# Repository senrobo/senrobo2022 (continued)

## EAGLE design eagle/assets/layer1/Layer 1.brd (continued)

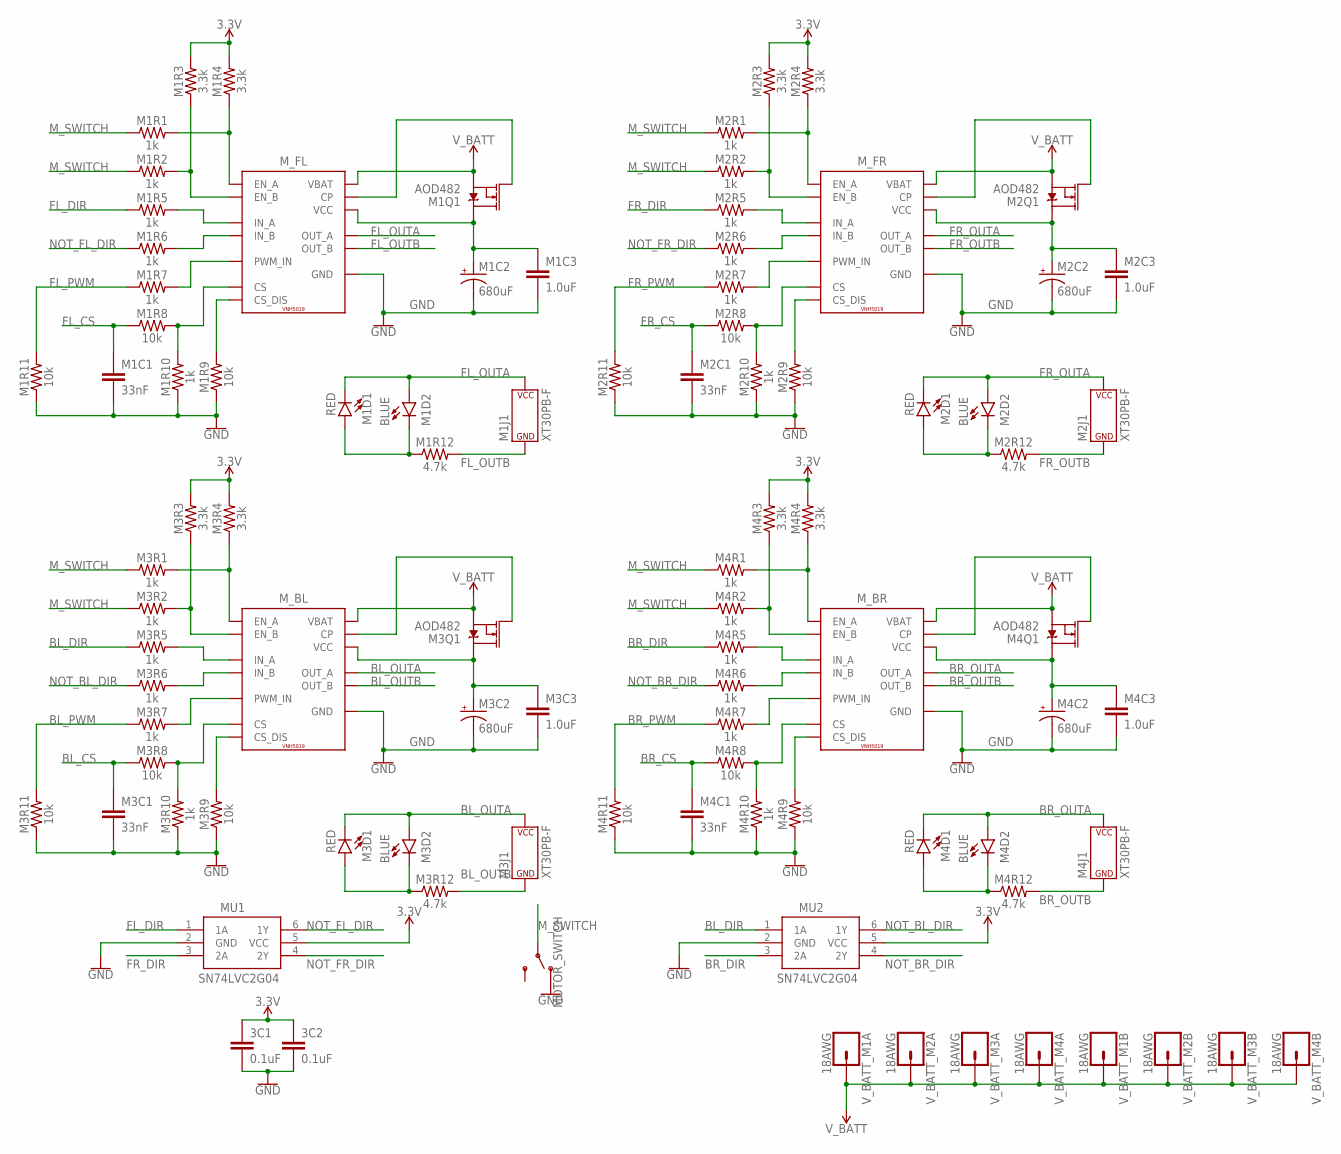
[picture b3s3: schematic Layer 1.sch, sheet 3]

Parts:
3C1, 3C2: 0.1uF; C0603
M1C1, M2C1, M3C1, M4C1: 33nF; C0603
M1C2, M2C2, M3C2, M4C2: 680uF; 3.5MM_CAP
M1C3, M2C3, M3C3, M4C3: 1.0uF; C0603
M1D1, M2D1, M3D1, M4D1: RED; LED-0603
M1D2, M2D2, M3D2, M4D2: BLUE; LED-0603
M1J1, M2J1, M3J1, M4J1: XT30PB-F
M1Q1, M2Q1, M3Q1, M4Q1: AOD482; DPAK
M1R1, M1R2, M1R5, M1R6, M1R7, M1R10, M2R1, M2R2, M2R5, M2R6, M2R7, M2R10, M3R1, M3R2, M3R5, M3R6, M3R7, M3R10, M4R1, M4R2, M4R5, M4R6, M4R7, M4R10: 1k; R0603
M1R3, M1R4, M2R3, M2R4, M3R3, M3R4, M4R3, M4R4: 3.3k; R0603
M1R8, M1R9, M1R11, M2R8, M2R9, M2R11, M3R8, M3R9, M3R11, M4R8, M4R9, M4R11: 10k; R0603
M1R12, M2R12, M3R12, M4R12: 4.7k; R0603
MOTOR_SWITCH: SWITCH-SPDT-PTH-11.6X4.0MM-LOCK; SWITCH_SPDT_PTH_11.6X4.0MM_LOCK
MU1, MU2: SN74LVC2G04DBVR; SOT23-6
M_BL: VNH5019; POWERSO-30
M_BR: VNH5019; POWERSO-30
M_FL: VNH5019; POWERSO-30
M_FR: VNH5019; POWERSO-30
V_BATT_M1A, V_BATT_M1B, V_BATT_M2A, V_BATT_M2B, V_BATT_M3A, V_BATT_M3B, V_BATT_M4A, V_BATT_M4B: 18AWG

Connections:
3.3V: 3C1.1, 3C2.1, M1R3.2, M1R4.2, M2R3.2, M2R4.2, M3R3.2, M3R4.2, M4R3.2, M4R4.2, MU1.5 (VCC), MU2.5 (VCC); also elsewhere on the board
BL_CS: M3C1.1, M3R8.1; also elsewhere on the board
BL_DIR: M3R5.1, MU2.1 (1A); also elsewhere on the board
BL_OUTA: M3D1.C, M3D2.A, M3J1.+ (V+), M_BL.P1 (OUT_A), M_BL.P25 (OUT_A), M_BL.P30 (OUT_A), M_BL.P$1 (OUT_A), M_BL.P$2 (OUT_A), M_BL.P$3 (OUT_A), M_BL.P$4 (OUT_A), M_BL.P$5 (OUT_A), M_BL.P$6 (OUT_A), M_BL.P$7 (OUT_A), M_BL.P$8 (OUT_A), M_BL.P$9 (OUT_A), M_BL.SLUG2 (OUT_A)
BL_OUTB: M3J1.- (V-), M3R12.2, M_BL.P15 (OUT_B), M_BL.P16 (OUT_B), M_BL.P21 (OUT_B), M_BL.P$10 (OUT_B), M_BL.P$11 (OUT_B), M_BL.P$12 (OUT_B), M_BL.P$13 (OUT_B), M_BL.P$14 (OUT_B), M_BL.P$15 (OUT_B), M_BL.P$16 (OUT_B), M_BL.P$17 (OUT_B), M_BL.P$18 (OUT_B), M_BL.SLUG3 (OUT_B)
BL_PWM: M3R7.1, M3R11.2; also elsewhere on the board
BR_CS: M4C1.1, M4R8.1; also elsewhere on the board
BR_DIR: M4R5.1, MU2.3 (2A); also elsewhere on the board
BR_OUTA: M4D1.C, M4D2.A, M4J1.+ (V+), M_BR.P1 (OUT_A), M_BR.P25 (OUT_A), M_BR.P30 (OUT_A), M_BR.P$1 (OUT_A), M_BR.P$2 (OUT_A), M_BR.P$3 (OUT_A), M_BR.P$4 (OUT_A), M_BR.P$5 (OUT_A), M_BR.P$6 (OUT_A), M_BR.P$7 (OUT_A), M_BR.P$8 (OUT_A), M_BR.P$9 (OUT_A), M_BR.SLUG2 (OUT_A)
BR_OUTB: M4J1.- (V-), M4R12.2, M_BR.P15 (OUT_B), M_BR.P16 (OUT_B), M_BR.P21 (OUT_B), M_BR.P$10 (OUT_B), M_BR.P$11 (OUT_B), M_BR.P$12 (OUT_B), M_BR.P$13 (OUT_B), M_BR.P$14 (OUT_B), M_BR.P$15 (OUT_B), M_BR.P$16 (OUT_B), M_BR.P$17 (OUT_B), M_BR.P$18 (OUT_B), M_BR.SLUG3 (OUT_B)
BR_PWM: M4R7.1, M4R11.2; also elsewhere on the board
FL_CS: M1C1.1, M1R8.1; also elsewhere on the board
FL_DIR: M1R5.1, MU1.1 (1A); also elsewhere on the board
FL_OUTA: M1D1.C, M1D2.A, M1J1.+ (V+), M_FL.P1 (OUT_A), M_FL.P25 (OUT_A), M_FL.P30 (OUT_A), M_FL.P$1 (OUT_A), M_FL.P$2 (OUT_A), M_FL.P$3 (OUT_A), M_FL.P$4 (OUT_A), M_FL.P$5 (OUT_A), M_FL.P$6 (OUT_A), M_FL.P$7 (OUT_A), M_FL.P$8 (OUT_A), M_FL.P$9 (OUT_A), M_FL.SLUG2 (OUT_A)
FL_OUTB: M1J1.- (V-), M1R12.2, M_FL.P15 (OUT_B), M_FL.P16 (OUT_B), M_FL.P21 (OUT_B), M_FL.P$10 (OUT_B), M_FL.P$11 (OUT_B), M_FL.P$12 (OUT_B), M_FL.P$13 (OUT_B), M_FL.P$14 (OUT_B), M_FL.P$15 (OUT_B), M_FL.P$16 (OUT_B), M_FL.P$17 (OUT_B), M_FL.P$18 (OUT_B), M_FL.SLUG3 (OUT_B)
FL_PWM: M1R7.1, M1R11.2; also elsewhere on the board
FR_CS: M2C1.1, M2R8.1; also elsewhere on the board
FR_DIR: M2R5.1, MU1.3 (2A); also elsewhere on the board
FR_OUTA: M2D1.C, M2D2.A, M2J1.+ (V+), M_FR.P1 (OUT_A), M_FR.P25 (OUT_A), M_FR.P30 (OUT_A), M_FR.P$1 (OUT_A), M_FR.P$2 (OUT_A), M_FR.P$3 (OUT_A), M_FR.P$4 (OUT_A), M_FR.P$5 (OUT_A), M_FR.P$6 (OUT_A), M_FR.P$7 (OUT_A), M_FR.P$8 (OUT_A), M_FR.P$9 (OUT_A), M_FR.SLUG2 (OUT_A)
FR_OUTB: M2J1.- (V-), M2R12.2, M_FR.P15 (OUT_B), M_FR.P16 (OUT_B), M_FR.P21 (OUT_B), M_FR.P$10 (OUT_B), M_FR.P$11 (OUT_B), M_FR.P$12 (OUT_B), M_FR.P$13 (OUT_B), M_FR.P$14 (OUT_B), M_FR.P$15 (OUT_B), M_FR.P$16 (OUT_B), M_FR.P$17 (OUT_B), M_FR.P$18 (OUT_B), M_FR.SLUG3 (OUT_B)
FR_PWM: M2R7.1, M2R11.2; also elsewhere on the board
GND: 3C1.2, 3C2.2, M1C1.2, M1C2.2 (-), M1C3.2, M1R9.1, M1R10.1, M1R11.1, M2C1.2, M2C2.2 (-), M2C3.2, M2R9.1, M2R10.1, M2R11.1, M3C1.2, M3C2.2 (-), M3C3.2, M3R9.1, M3R10.1, M3R11.1, M4C1.2, M4C2.2 (-), M4C3.2, M4R9.1, M4R10.1, M4R11.1, MOTOR_SWITCH.1 (O), MU1.2 (GND), MU2.2 (GND), M_BL.P18 (GND), M_BL.P19 (GND), M_BL.P20 (GND), M_BL.P26 (GND), M_BL.P27 (GND), M_BL.P28 (GND), M_BR.P18 (GND), M_BR.P19 (GND), M_BR.P20 (GND), M_BR.P26 (GND), M_BR.P27 (GND), M_BR.P28 (GND), M_FL.P18 (GND), M_FL.P19 (GND), M_FL.P20 (GND), M_FL.P26 (GND), M_FL.P27 (GND), M_FL.P28 (GND), M_FR.P18 (GND), M_FR.P19 (GND), M_FR.P20 (GND), M_FR.P26 (GND), M_FR.P27 (GND), M_FR.P28 (GND); also elsewhere on the board
M_SWITCH: M1R1.1, M1R2.1, M2R1.1, M2R2.1, M3R1.1, M3R2.1, M4R1.1, M4R2.1, MOTOR_SWITCH.2
unnamed: M1R1.2, M1R4.1, M_FL.P5 (EN_A)
unnamed: M1R2.2, M1R3.1, M_FL.P9 (EN_B)
unnamed: M1R5.2, M_FL.P4 (IN_A)
unnamed: M1R6.2, M_FL.P10 (IN_B)
unnamed: M1R7.2, M_FL.P7 (PWM_IN)
unnamed: M1R8.2, M1R10.2, M_FL.P8 (CS)
unnamed: M1R9.2, M_FL.P6 (CS_DIS)
unnamed: M1C2.1 (+), M1C3.1, M1Q1.4 (D), M_FL.P3 (VCC), M_FL.P13 (VCC), M_FL.P23 (VCC), M_FL.P$19 (VCC), M_FL.P$20 (VCC), M_FL.P$21 (VCC), M_FL.P$22 (VCC), M_FL.P$23 (VCC), M_FL.P$24 (VCC), M_FL.P$25 (VCC), M_FL.P$26 (VCC), M_FL.P$27 (VCC), M_FL.P$28 (VCC), M_FL.SLUG1 (VCC)
unnamed: M1Q1.1 (G), M_FL.P11 (CP)
unnamed: M2R2.2, M2R3.1, M_FR.P9 (EN_B)
unnamed: M1D1.A, M1D2.C, M1R12.1
unnamed: M2R1.2, M2R4.1, M_FR.P5 (EN_A)
unnamed: M2R6.2, M_FR.P10 (IN_B)
unnamed: M2R5.2, M_FR.P4 (IN_A)
unnamed: M2R7.2, M_FR.P7 (PWM_IN)
unnamed: M2R8.2, M2R10.2, M_FR.P8 (CS)
unnamed: M2R9.2, M_FR.P6 (CS_DIS)
unnamed: M2C2.1 (+), M2C3.1, M2Q1.4 (D), M_FR.P3 (VCC), M_FR.P13 (VCC), M_FR.P23 (VCC), M_FR.P$19 (VCC), M_FR.P$20 (VCC), M_FR.P$21 (VCC), M_FR.P$22 (VCC), M_FR.P$23 (VCC), M_FR.P$24 (VCC), M_FR.P$25 (VCC), M_FR.P$26 (VCC), M_FR.P$27 (VCC), M_FR.P$28 (VCC), M_FR.SLUG1 (VCC)
unnamed: M2Q1.1 (G), M_FR.P11 (CP)
unnamed: M3R2.2, M3R3.1, M_BL.P9 (EN_B)
unnamed: M2D1.A, M2D2.C, M2R12.1
unnamed: M3R1.2, M3R4.1, M_BL.P5 (EN_A)
unnamed: M3R6.2, M_BL.P10 (IN_B)
unnamed: M3R5.2, M_BL.P4 (IN_A)
unnamed: M3R7.2, M_BL.P7 (PWM_IN)
unnamed: M3R8.2, M3R10.2, M_BL.P8 (CS)
unnamed: M3R9.2, M_BL.P6 (CS_DIS)
unnamed: M3C2.1 (+), M3C3.1, M3Q1.4 (D), M_BL.P3 (VCC), M_BL.P13 (VCC), M_BL.P23 (VCC), M_BL.P$19 (VCC), M_BL.P$20 (VCC), M_BL.P$21 (VCC), M_BL.P$22 (VCC), M_BL.P$23 (VCC), M_BL.P$24 (VCC), M_BL.P$25 (VCC), M_BL.P$26 (VCC), M_BL.P$27 (VCC), M_BL.P$28 (VCC), M_BL.SLUG1 (VCC)
unnamed: M3Q1.1 (G), M_BL.P11 (CP)
unnamed: M4R2.2, M4R3.1, M_BR.P9 (EN_B)
unnamed: M4R1.2, M4R4.1, M_BR.P5 (EN_A)
unnamed: M4R6.2, M_BR.P10 (IN_B)
unnamed: M4R5.2, M_BR.P4 (IN_A)
unnamed: M4R7.2, M_BR.P7 (PWM_IN)
unnamed: M3D1.A, M3D2.C, M3R12.1
unnamed: M4R8.2, M4R10.2, M_BR.P8 (CS)
unnamed: M4R9.2, M_BR.P6 (CS_DIS)
unnamed: M4C2.1 (+), M4C3.1, M4Q1.4 (D), M_BR.P3 (VCC), M_BR.P13 (VCC), M_BR.P23 (VCC), M_BR.P$19 (VCC), M_BR.P$20 (VCC), M_BR.P$21 (VCC), M_BR.P$22 (VCC), M_BR.P$23 (VCC), M_BR.P$24 (VCC), M_BR.P$25 (VCC), M_BR.P$26 (VCC), M_BR.P$27 (VCC), M_BR.P$28 (VCC), M_BR.SLUG1 (VCC)
unnamed: M4Q1.1 (G), M_BR.P11 (CP)
unnamed: M4D1.A, M4D2.C, M4R12.1
NOT_BL_DIR: M3R6.1, MU2.6 (1Y)
NOT_BR_DIR: M4R6.1, MU2.4 (2Y)
NOT_FL_DIR: M1R6.1, MU1.6 (1Y)
NOT_FR_DIR: M2R6.1, MU1.4 (2Y)
V_BATT: M1Q1.3 (S), M2Q1.3 (S), M3Q1.3 (S), M4Q1.3 (S), M_BL.P12 (VBAT), M_BR.P12 (VBAT), M_FL.P12 (VBAT), M_FR.P12 (VBAT), V_BATT_M1A.P$1, V_BATT_M1B.P$1, V_BATT_M2A.P$1, V_BATT_M2B.P$1, V_BATT_M3A.P$1, V_BATT_M3B.P$1, V_BATT_M4A.P$1, V_BATT_M4B.P$1; also elsewhere on the board

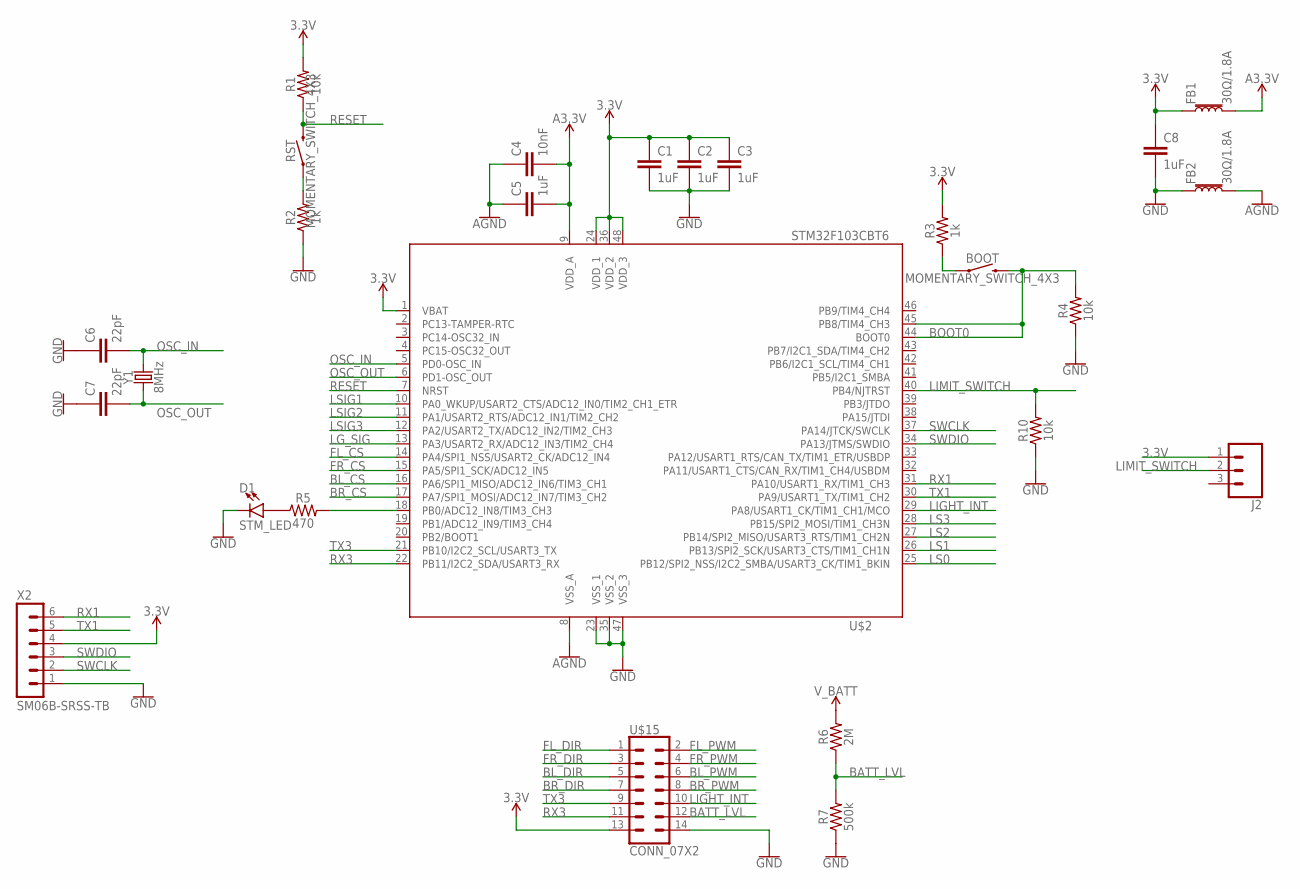
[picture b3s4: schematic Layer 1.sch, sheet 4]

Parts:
BOOT: MOMENTARY_SWITCH_4X3
C1, C2, C3, C5, C8: 1uF; C0603
C4: 10nF; C0603
C6, C7: 22pF; C0603
D1: STM_LED; LED-0603
FB1, FB2: 30Ω/1.8A; 0603
J2: CONN_03LOCK_NO_SILK; 1X03_LOCK_NO_SILK
R1, R4, R10: 10k; R0603
R2, R3: 1k; R0603
R5: 470; R0603
R6: 2M; R0603
R7: 500k; R0603
RST: MOMENTARY_SWITCH_4X3
U$2: STM32F103CBT6; LQFP48
U$15: CONN_07X2; 2X7
X2: SM06B-SRSS-TB
Y1: 8MHz; CRYSTAL-SMD-5X3.2-2PAD

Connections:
3.3V: C1.1, C2.1, C3.1, C8.1, FB1.1, J2.1, R1.2, R3.2, U$2.1 (VBAT), U$2.24 (VDD_1), U$2.36 (VDD_2), U$2.48 (VDD_3), U$15.13, X2.4; also elsewhere on the board
AGND: C4.1, C5.1, FB2.2, U$2.8 (VSS_A); also elsewhere on the board
BATT_LVL: R6.1, R7.2, U$15.12
BL_CS: U$2.16 (PA6/SPI1_MISO/ADC12_IN6/TIM3_CH1); also elsewhere on the board
BL_DIR: U$15.5; also elsewhere on the board
BL_PWM: U$15.6; also elsewhere on the board
BOOT0: BOOT.P$2 (2), R4.2, U$2.44 (BOOT0), U$2.45 (PB8/TIM4_CH3)
BR_CS: U$2.17 (PA7/SPI1_MOSI/ADC12_IN7/TIM3_CH2); also elsewhere on the board
BR_DIR: U$15.7; also elsewhere on the board
BR_PWM: U$15.8; also elsewhere on the board
FL_CS: U$2.14 (PA4/SPI1_NSS/USART2_CK/ADC12_IN4); also elsewhere on the board
FL_DIR: U$15.1; also elsewhere on the board
FL_PWM: U$15.2; also elsewhere on the board
FR_CS: U$2.15 (PA5/SPI1_SCK/ADC12_IN5); also elsewhere on the board
FR_DIR: U$15.3; also elsewhere on the board
FR_PWM: U$15.4; also elsewhere on the board
GND: C1.2, C2.2, C3.2, C6.1, C7.1, C8.2, D1.C, FB2.1, R2.1, R4.1, R7.1, R10.1, U$2.23 (VSS_1), U$2.35 (VSS_2), U$2.47 (VSS_3), U$15.14, X2.1; also elsewhere on the board
LG_SIG: U$2.13 (PA3/USART2_RX/ADC12_IN3/TIM2_CH4); also elsewhere on the board
LIGHT_INT: U$2.29 (PA8/USART1_CK/TIM1_CH1/MCO), U$15.10
LIMIT_SWITCH: J2.2, R10.2, U$2.40 (PB4/NJTRST)
LS0: U$2.25 (PB12/SPI2_NSS/I2C2_SMBA/USART3_CK/TIM1_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); also elsewhere on the board
LS1: U$2.26 (PB13/SPI2_SCK/USART3_CTS/TIM1_CH1N); also elsewhere on the board
LS2: U$2.27 (PB14/SPI2_MISO/USART3_RTS/TIM1_CH2N); also elsewhere on the board
LS3: U$2.28 (PB15/SPI2_MOSI/TIM1_CH3N); also elsewhere on the board
LSIG1: U$2.10 (PA0_WKUP/USART2_CTS/ADC12_IN0/TIM2_CH1_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); also elsewhere on the board
LSIG2: U$2.11 (PA1/USART2_RTS/ADC12_IN1/TIM2_CH2); also elsewhere on the board
LSIG3: U$2.12 (PA2/USART2_TX/ADC12_IN2/TIM2_CH3); also elsewhere on the board
unnamed: R2.2, RST.P$1 (1)
unnamed: BOOT.P$1 (1), R3.1
unnamed: R5.2, U$2.18 (PB0/ADC12_IN8/TIM3_CH3)
unnamed: D1.A, R5.1
OSC_IN: C6.2, U$2.5 (PD0-OSC_IN), Y1.P$2 (2)
OSC_OUT: C7.2, U$2.6 (PD1-OSC_OUT), Y1.P$1 (1)
RESET: R1.1, RST.P$2 (2), U$2.7 (NRST)
RX1: U$2.31 (PA10/USART1_RX/TIM1_CH3), X2.6
RX3: U$2.22 (PB11/I2C2_SDA/USART3_RX), U$15.11
SWCLK: U$2.37 (PA14/JTCK/SWCLK), X2.2
SWDIO: U$2.34 (PA13/JTMS/SWDIO), X2.3
TX1: U$2.30 (PA9/USART1_TX/TIM1_CH2), X2.5
TX3: U$2.21 (PB10/I2C2_SCL/USART3_TX), U$15.9
VCCA: C4.2, C5.2, FB1.2, U$2.9 (VDD_A); also elsewhere on the board
V_BATT: R6.2; also elsewhere on the board

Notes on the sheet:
LIMIT_SWITCH

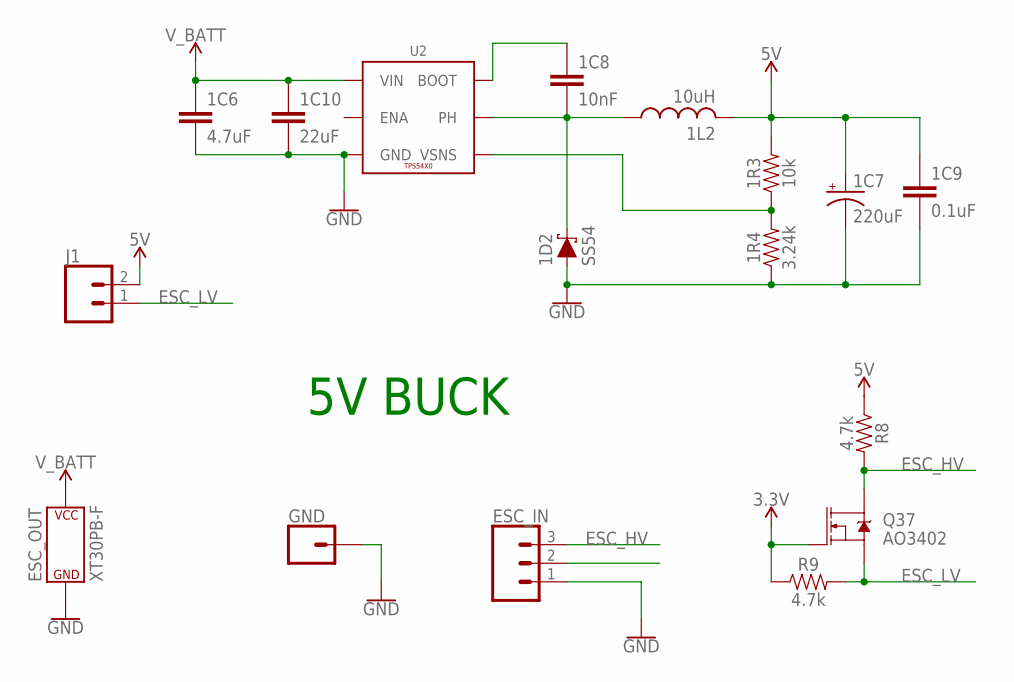
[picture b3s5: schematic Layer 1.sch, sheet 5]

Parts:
1C6: 4.7uF; C0603
1C7: 220uF; EIA7343
1C8: 10nF; C0603
1C9: 0.1uF; C0603
1C10: 22uF; C1210
1D2: SS54; SMA-DIODE
1L2: 10uH; SWPA8040
1R3: 10k; R0603
1R4: 3.24k; R0603
ESC_IN: CONN_03LOCK; 1X03_LOCK
ESC_OUT: XT30PB-F
GND: CONN_01; 1X01
J1: CONN_02LOCK; 1X02_LOCK
Q37: AO3402; SOT23-3
R8, R9: 4.7k; R0603
U2: TPS54X0; POWERPAD-SOIC-8

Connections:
3.3V1: Q37.1 (G), R9.1
5V: 1C7.A (+), 1C9.1, 1L2.P2 (2), 1R3.2, J1.2, R8.1
ESC_HV: ESC_IN.3, Q37.3 (D), R8.2
ESC_LV: J1.1, Q37.2 (S), R9.2
GND: 1C6.2, 1C7.C (-), 1C9.2, 1C10.2, 1D2.A, 1R4.1, ESC_IN.1, ESC_OUT.- (V-), GND.1, U2.6 (GND), U2.9 (GND), U2.P$1 (GND), U2.P$2 (GND), U2.P$3 (GND), U2.P$4 (GND), U2.P$5 (GND), U2.P$6 (GND); also elsewhere on the board
unnamed: 1C8.2, 1D2.C, 1L2.P1 (1), U2.8 (PH)
unnamed: 1R3.1, 1R4.2, U2.4 (VSNS)
unnamed: 1C8.1, U2.1 (BOOT)
V_BATT: 1C6.1, 1C10.1, ESC_OUT.+ (V+), U2.7 (VIN); also elsewhere on the board

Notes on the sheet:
5V BUCK

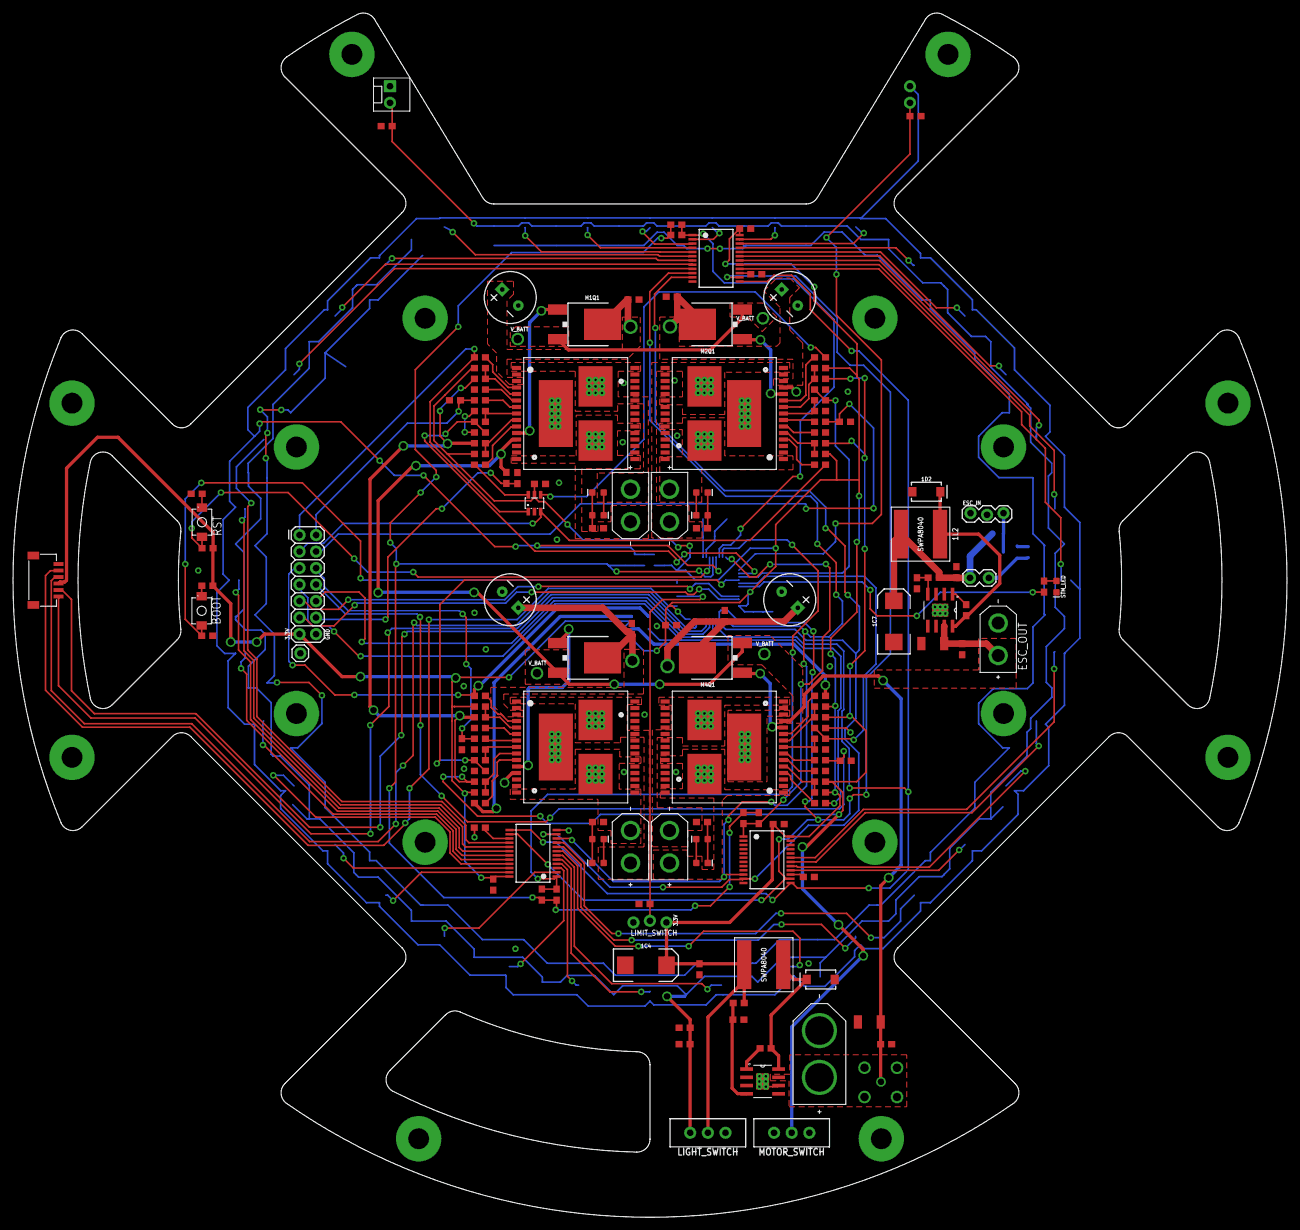
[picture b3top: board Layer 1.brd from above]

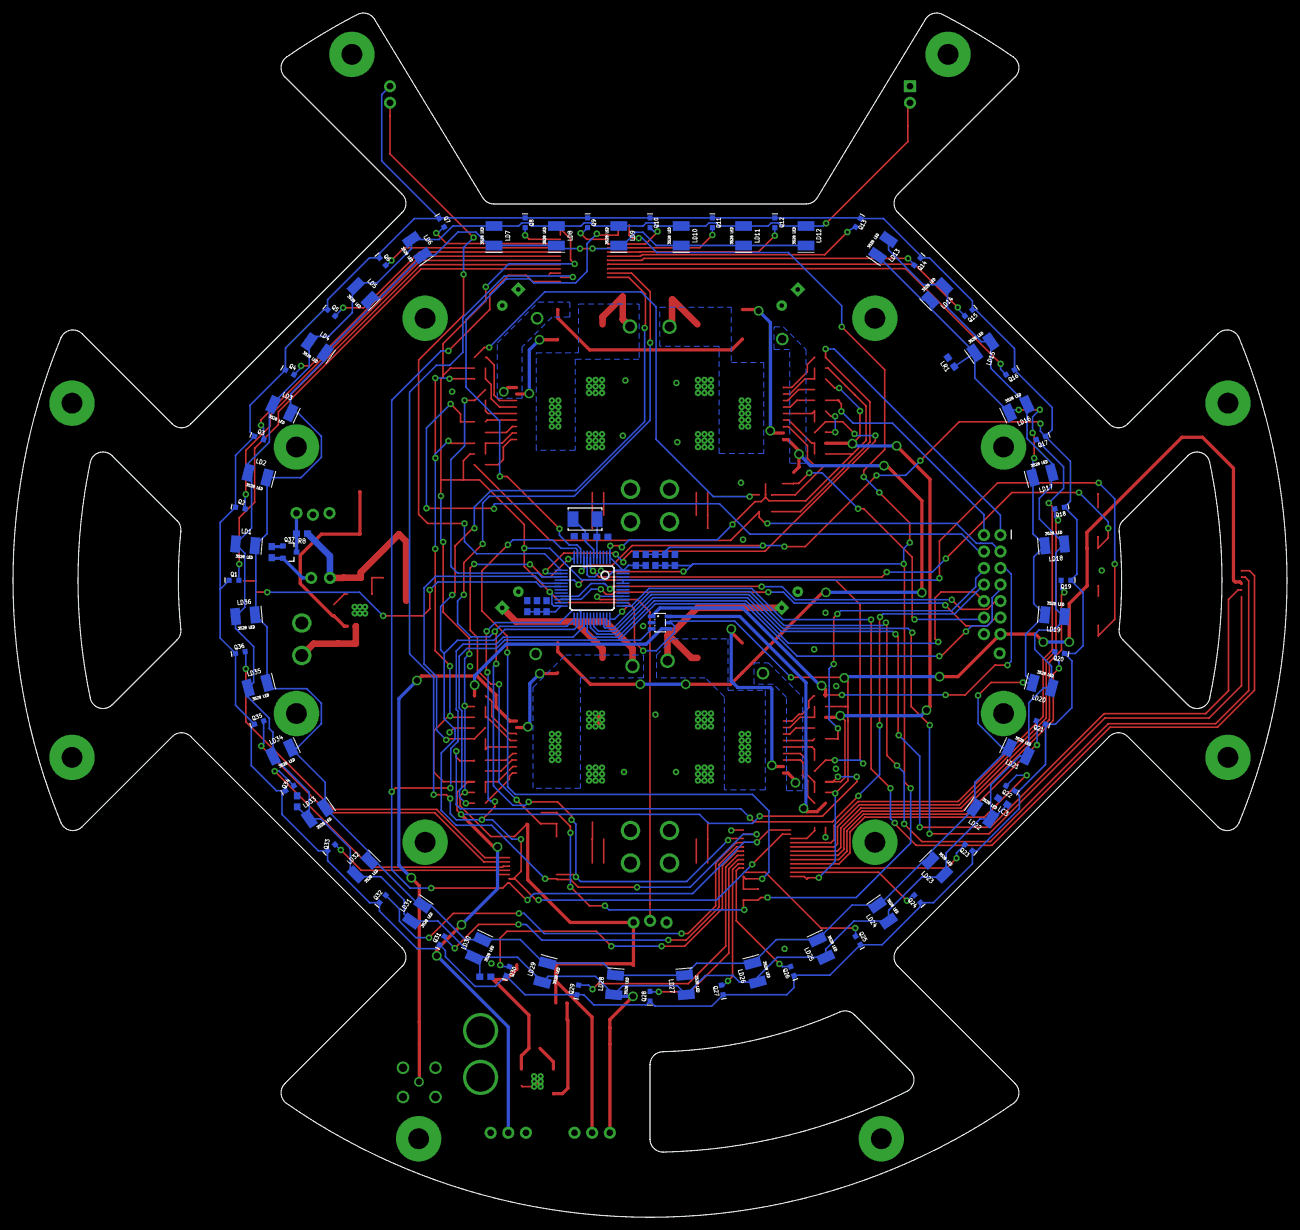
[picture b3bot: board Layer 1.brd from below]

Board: 2 copper layers, 196.0 x 185.3 mm, 245 parts (92 on the bottom side), 146 nets.

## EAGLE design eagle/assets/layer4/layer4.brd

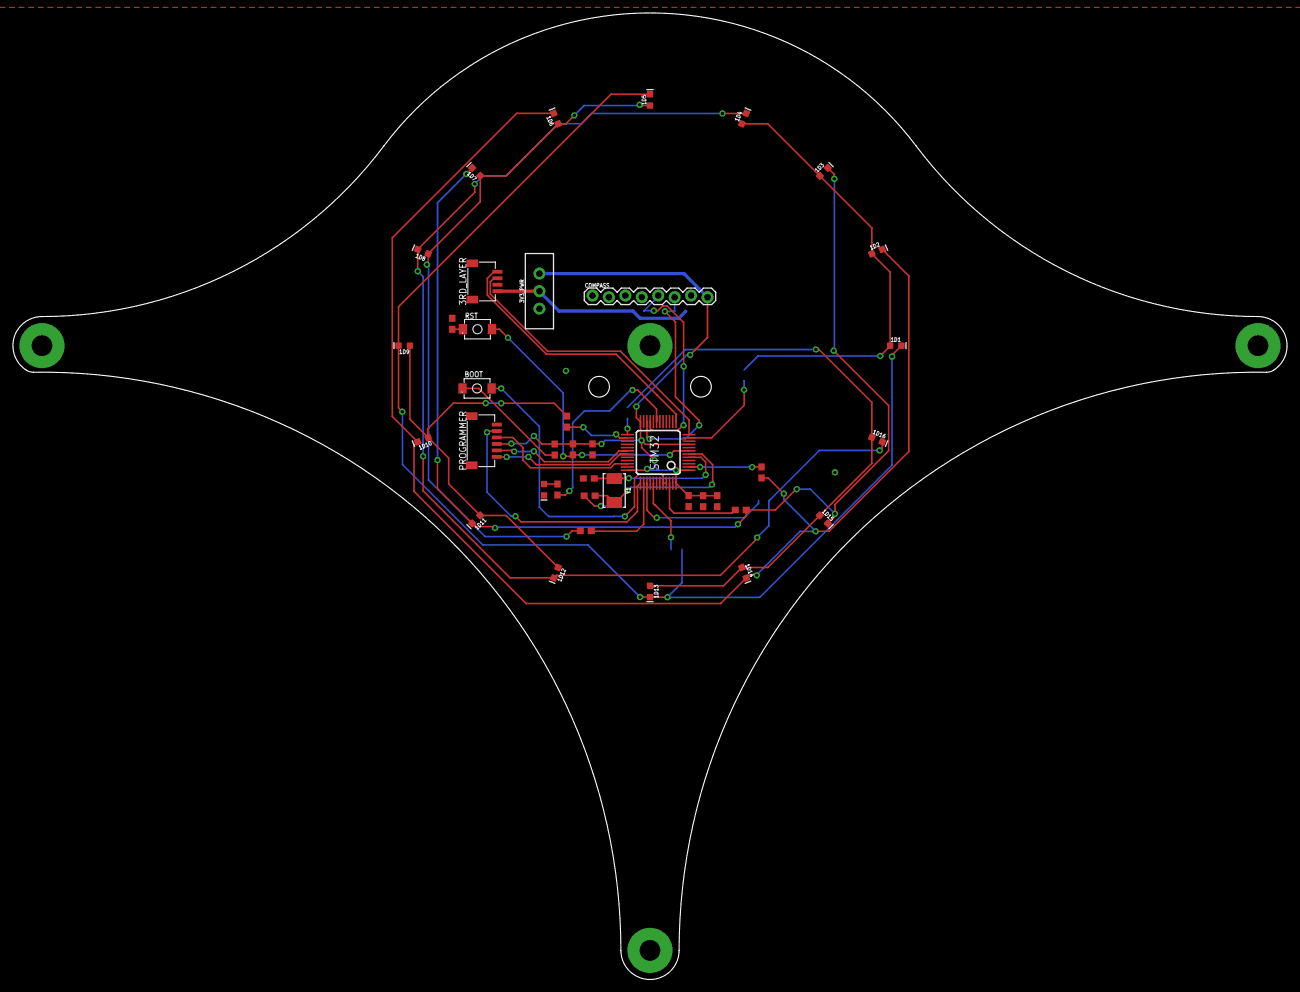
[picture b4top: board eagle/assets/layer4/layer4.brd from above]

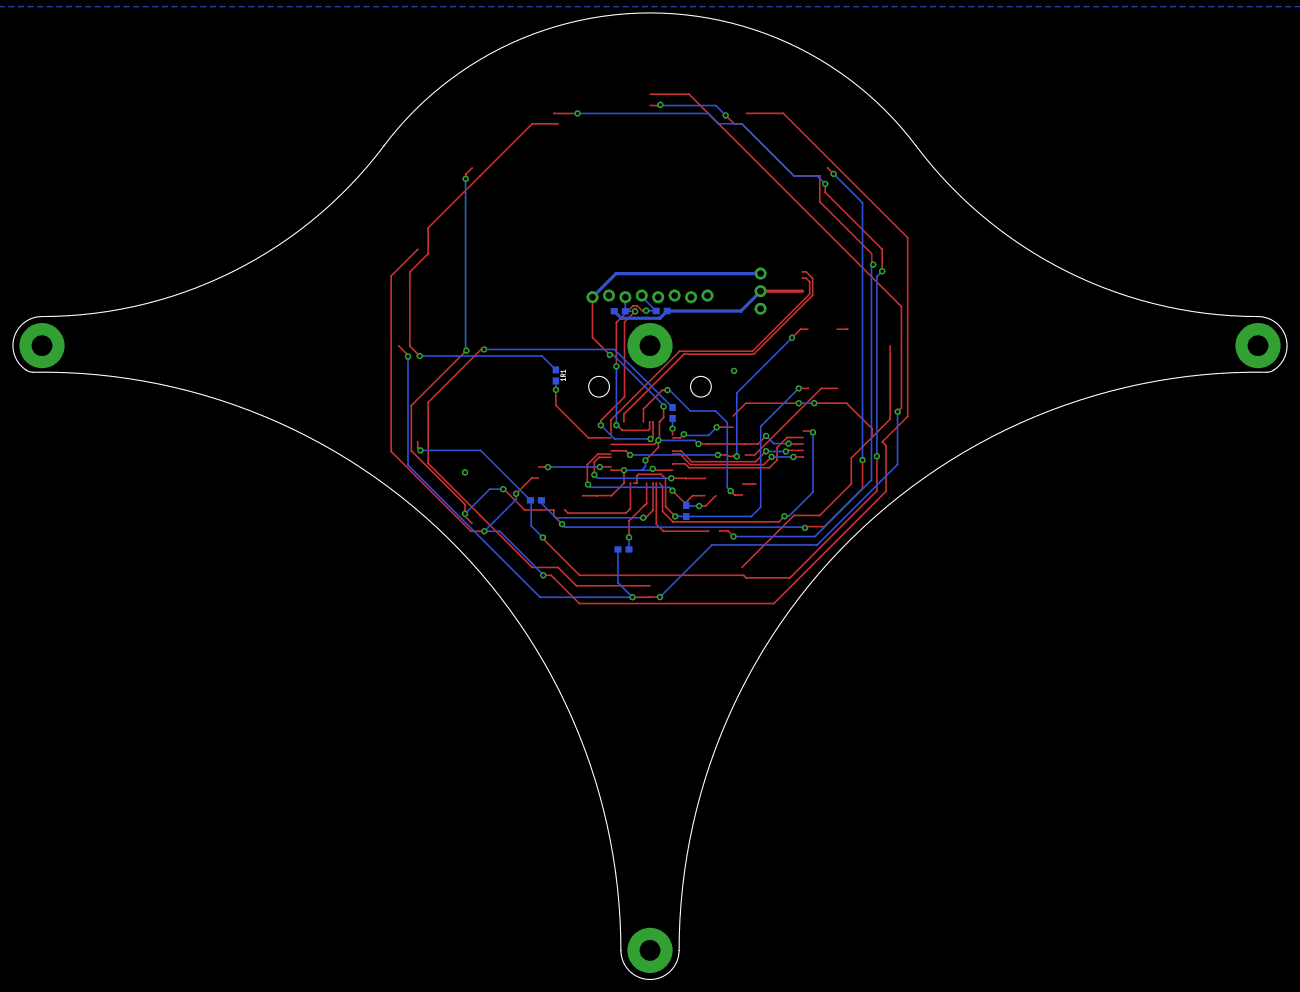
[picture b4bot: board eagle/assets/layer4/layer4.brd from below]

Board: 2 copper layers, 197.0 x 149.4 mm, 46 parts (7 on the bottom side), 35 nets.

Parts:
1D1, 1D2, 1D3, 1D4, 1D5, 1D6, 1D7, 1D8, 1D9, 1D10, 1D11, 1D12, 1D13, 1D14, 1D15, 1D16: LED-0603
1R1, 1R2, 1R3, 1R4, 1R5, 1R6, 1R7, 1R8: 470; R0603
3RD_LAYER: SM04B-SRSS-TB
3V3_PWR: SWITCH_SPDT_PTH_11.6X4.0MM_LOCK
BOOT: MOMENTARY_SWITCH_4X3
C1, C2, C3, C5: 1uF; C0603
C6, C7: 22pF; C0603
COMPASS: BNO055
D1: BLUE; LED-0603
PROGRAMMER: SM06B-SRSS-TB
R1, R4: 10k; R0603
R2, R3, R5: 1k; R0603
R6, R7: 4.7k; 0603
RST: MOMENTARY_SWITCH_4X3
STM32: STM32F103CBT6; LQFP48
Y1: 8MHz; CRYSTAL-SMD-5X3.2-2PAD

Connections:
3.3V: 3RD_LAYER.4, 3V3_PWR.2, R6.2, R7.2
3V3_SWITCH: 3V3_PWR.1, C1.1, C2.1, C3.1, C5.2, COMPASS.8, PROGRAMMER.4, R1.2, R3.2, STM32.1, STM32.9, STM32.24, STM32.36, STM32.48
BOOT0: BOOT.P$2, R4.2, STM32.44, STM32.45
GND: 3RD_LAYER.3, C1.2, C2.2, C3.2, C5.1, C6.1, C7.1, COMPASS.7, D1.C, PROGRAMMER.1, R2.1, R4.1, STM32.8, STM32.23, STM32.35, STM32.47
L1C: 1R5.1, STM32.41
L1R: 1R1.2, STM32.11
L2C: 1R6.1, STM32.2
L2R: 1R2.2, STM32.38
L3C: 1R7.1, STM32.46
L3R: 1R3.2, STM32.26
L4C: 1R8.1, STM32.39
L4R: 1R4.2, STM32.25
unnamed: 1D1.A, 1D2.A, 1D3.A, 1D4.A, 1R1.1
unnamed: 1D1.C, 1D5.C, 1D9.C, 1D13.C, 1R5.2
unnamed: 1D5.A, 1D6.A, 1D7.A, 1D8.A, 1R2.1
unnamed: 1D9.A, 1D10.A, 1D11.A, 1D12.A, 1R3.1
unnamed: 1D13.A, 1D14.A, 1D15.A, 1D16.A, 1R4.1
unnamed: 1D2.C, 1D6.C, 1D10.C, 1D14.C, 1R6.2
unnamed: 1D3.C, 1D7.C, 1D11.C, 1D15.C, 1R7.2
unnamed: 1D4.C, 1D8.C, 1D12.C, 1D16.C, 1R8.2
unnamed: R2.2, RST.P$1
unnamed: BOOT.P$1, R3.1
unnamed: R5.2, STM32.19
unnamed: D1.A, R5.1
OSC_IN: C6.2, STM32.5, Y1.P$2
OSC_OUT: C7.2, STM32.6, Y1.P$1
RESET: R1.1, RST.P$2, STM32.7
RX1: PROGRAMMER.6, STM32.31
RX2: 3RD_LAYER.1, STM32.13
SCL2: COMPASS.5, R7.1, STM32.21
SDA2: COMPASS.6, R6.1, STM32.22
SWCLK: PROGRAMMER.2, STM32.37
SWDIO: PROGRAMMER.3, STM32.34
TX1: PROGRAMMER.5, STM32.30
TX2: 3RD_LAYER.2, STM32.12

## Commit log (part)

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2021-11-25 added layer1 and layer2 pdf
2021-11-25 moved v1 folder to .pdf folder
2021-11-25 added gcode and stl
2021-11-25 updated dribbler mount & plate, added dribbler spaces
2021-11-26 updated motor mount and added missing holes for motor to layer 2
2021-11-26 cool
2021-11-26 file
2021-11-26 eagle layer 3
2021-11-26 added layer 3
2021-11-26 updated eagle file
2021-11-26 Eagle
2021-11-27 Added excel
2021-11-27 Added Sketches
2021-11-27 layer 3
2021-11-27 Added stands
2021-11-27 I am done i think
2021-11-27 Added alu stands as alternative
2021-11-27 included sketches layer 3 n 4
2021-11-28 added dxf files for layer 3 and 4
2021-11-29 added docs folder
2021-11-29 added cam and dru folder
2021-11-29 final file
2021-11-29 autocad
2021-11-29 cancer pain in the ass
2021-11-30 edit
2021-12-01 layer 4 sch
2021-12-01 added assets: limitswitch.dwg
2021-12-01 layer 2
2021-12-01 added layer 4 file
2021-12-01 layer 3 update
2021-12-01 updated limitswitch.dwg
2021-12-01 more shit need to do
2021-12-01 about done
2021-12-01 done with layer 4
2021-12-01 changes to layout in layer 3
2021-12-01 change sch
2021-12-01 editied layers
2021-12-01 forgot to save
2021-12-02 added 2mm spacers
2021-12-02 switch hole
2021-12-02 modified layers 3 and 4
2021-12-02 knn smlj
2021-12-03 added blackflipswitch.stl
2021-12-03 added blackflipswitch.dwg asset
2021-12-03 changed layer 2 to 3 mount height
2021-12-03 handle sketches
2021-12-03 Layer 4 Sketches
2021-12-03 Added DXF
2021-12-03 added layers dxf
2021-12-03 balls
2021-12-03 lol ono
2021-12-06 added m3nut.dwg
2021-12-06 did sanity check on bot
2021-12-06 removed .pdf files
2021-12-06 removed .dxf sketches
2021-12-06 updated layer 3 dxf
2021-12-06 done with layer 3 schem
2021-12-08 fat fuck balls
2021-12-08 fuck you yun song
2021-12-08 suck my balls
2022-01-04 left with calculations
2022-01-04 homer monkey brain
2022-01-04 commit literally nothing
2022-01-11 modelled new kicker and updated layer1.dxf
2022-01-11 redoing the kicker
2022-01-12 modelled new kicker and created kicker parts stl files
2022-01-12 added cura profs
2022-01-13 removed fillet in the kicker
2022-01-13 redesigned kicker to second later
2022-01-14 kicker parts gcode
2022-01-14 kicker update
2022-01-14 added layer1v2
2022-01-14 re uploaded layer1v2.dxf
2022-01-14 added old folder in .dxf
2022-01-14 added old folder to .pdf
2022-01-14 added .pdf for each layers
2022-01-14 exported .pdf files to .ai
2022-01-15 added .iges and removed switch hole from layer 2
2022-01-15 Updated Layer 3 with new DXF
2022-01-15 Added word to handle
2022-01-17 Added layer 3pcb
2022-01-17 🚀🚀🚀 Edited Layer 3 and 4 Changed the positioning of the BT Module Change the positioning of the connectors
2022-01-17 😭fusion and autocad bully me
2022-01-18 🥰 Layer 3 Edits Changed oreintation of XH Connectors Shrunk the radius of IR Sensor
2022-01-18 🚒🔥Tired Added IR Guard
2022-01-18 💀 Edited IR Guard
2022-01-18 🛌 Imma head to bed
2022-01-19 💰 part list
2022-01-19 the fuck
2022-01-19 help
2022-01-19 clean
2022-01-19 somehow zeus doesnt upload eagle
2022-01-19 💀 Almost died again thank god hv backup
2022-01-19 fucked up
2022-01-19 🏭 Added CAM File 🏭
2022-01-19 added .zip folder
2022-01-19 added folder for icon
2022-01-20 😎 Added stuff done in readme
2022-01-20 tried gear in autocad but failed
2022-01-20 updated kicker to v4, corrected slanted faces on kicker
2022-01-20 updated kicker to v4, corrected slanted faces on kicker (recommit)
2022-01-20 added old directory in eagle/assets
2022-01-20 🥳🎇🎆🎉 Done with the mirror
2022-01-20 cut holes in layer 4 and added dxf layer 4 v2
2022-01-20 cut holes in layer 4 and added dxf layer 4 v2 (recommit)
2022-01-20 updated .gitignore in .dwg/final
2022-01-20 changed colours for layers in Final dwg
2022-01-20 edited kicker
2022-01-20 yeet
2022-01-20 penis
2022-01-20 🦅 Included Layer 4 new
2022-01-20 🦅 Edited Layer 3 Testing Git LFS
2022-01-20 edited Git LFS
2022-01-20 😩 fml
2022-01-21 renamed final files
2022-01-21 created layer4v3.dxf
2022-01-21 step
2022-01-21 add layer 4 .pdf and .ai
2022-01-21 added mg90s servo dwg model
2022-01-21 🏎 git push️
2022-01-21 halfway done with servo mount
2022-01-21 Made the servo mount Havent added holes
2022-01-21 🦅 Layer 3 AGAIN
2022-01-21 fuck me
2022-01-21 removed mouse sensor
2022-01-21 oh no
2022-01-21 depression
2022-01-22 depressionv2
2022-01-22 depressionv3
2022-01-22 depressionv4
2022-01-22 depressionv5
2022-01-22 depressionv6
2022-01-22 depressionv7
2022-01-22 edited layer 1
2022-01-24 cut holes in layer 2 and 3 for servo mount and update dxf (not plotted and no ai files yet)
2022-01-26 cut mirrored hole in layer 2
2022-01-26 recommit
2022-01-27 168 airwires left
2022-01-27 130 airwires left
2022-01-27 121 airwires left mostly stm32
2022-01-27 routed some to STEM32
2022-01-27 Added A shit ton of polygons arnd the motor
2022-01-27 Added a shit ton of polygons
2022-01-28 Brainfuck
2022-01-28 62 airwires
2022-01-28 63 airwires
2022-01-28 29 airwires left
2022-01-28 27 airwires left
2022-01-28 18 airwires left
2022-01-28 10 airwires left
2022-01-28 5 airwires left
2022-01-28 Done with layer 1
2022-01-28 fuck
2022-01-28 fuck eagle dying again
2022-01-29 braindead
2022-01-29 fixed
2022-02-05 edited layer 1 holes to vias
2022-02-05 redid layer 1
2022-02-05 redid layer 1 paining
2022-02-05 removed some words
2022-02-05 edited via size
2022-02-06 edited layer 3 bt module
2022-02-06 edited layer 3 vias
2022-02-07 retarded 🦅
2022-02-08 layer 2 dxf not completed
2022-02-09 updated layer 5 dxf (v5)
2022-02-09 taobao
2022-02-09 layer2v6
2022-02-09 exported new stl files
2022-02-09 sliced gcode file for kicker and servo parts
2022-02-09 incomplete
2022-02-09 all parts here but quite messy
2022-02-10 retarded taobao
2022-02-11 drew new layer 2 dxf (v7)
2022-02-11 dgfhrg
2022-02-11 updated all layers dxf
2022-02-11 updated all layers dxf recommit
2022-02-11 moved layer 1
2022-02-11 moved layer 1 again
2022-02-11 layer1v8
2022-02-11 incomplete layer 1
2022-02-11 completed layer1, vincent check now
2022-02-11 aligned layers 3 and 4 to geom center in dxf files
2022-02-13 retarded 🦅 just moved one line
2022-02-18 layers 1, 3, 4 complete, layer 2 need to change holes to green color thingy?
2022-02-18 stuff added to layer2
2022-02-21 retarded 🦅 Layer 1 Finished Checking
2022-02-21 deleted useless fiels
2022-02-21 Added limit switch
2022-02-21 layer 1 v10 dxf
2022-02-21 layer2 v9 dxf
2022-02-21 Edited PCB for larger catchment area
2022-02-21 fixed issues on layer 1
2022-02-21 Modified more stuff
2022-02-21 Fixed a wire stub
2022-02-21 Fixed more stuff
2022-02-22 layer2 v10 dxf
2022-02-22 Retarded eagle
2022-02-22 Final Check
2022-02-22 Added GND Connector
2022-02-22 More taobao
2022-02-23 Edited Layer 4
2022-02-23 primt file
2022-02-23 Edited PCB
2022-02-23 Final PCB
2022-02-23 Vincent please dont touch pcb anymore focus on studies
2022-02-23 Made all the standoff vias GND
2022-02-23 Undid changes
2022-02-23 Removed Motor Ground and Added battery mount holes
2022-02-23 fucking done pls vincent dont touch it AGAIN
2022-02-24 Removed Layer 4 and moved all layer 4 to 3
2022-02-24 Redoing the positioning of the motor driver power supply and changed the battery mount holes
2022-02-24 Did FL and FR Motors
2022-02-24 Did BL Motor
2022-02-24 Finished
2022-02-25 Depressed 🦅
2022-02-25 Depressed 🦅 Layer 1
2022-02-25 moved v10layer to old folder
2022-02-25 All layers have frames
2022-02-25 layer4v4 dxf
2022-02-25 Done layer 1
2022-02-25 gerber
2022-02-26 layer 2 update v12
2022-02-26 fuck i do eagle again
2022-02-26 final
2022-02-28 Changing 3.6 to 4.0
2022-02-28 final integration of teensy 4 to board
2022-02-28 added teensy 4 lbr
2022-02-28 cut more holes beech
2022-03-01 Edited teensy 4 pin out
2022-03-01 Added Cura settings
2022-03-01 Sent to SRC
2022-03-02 logo
2022-03-02 Arduino
2022-03-02 fuck man i paid 4 bucks for this
2022-03-02 graphics
2022-03-03 Programming
2022-03-04 servo mount
2022-03-04 profile
2022-03-04 things
2022-03-04 Edited cura
2022-03-04 servo mount done
2022-03-04 lmao servo mount?
2022-03-04 gcode
2022-03-06 servo mount design new
2022-03-06 new layer 1.5
2022-03-06 mesh design cutouts in layer1.5
2022-03-08 new slope design
2022-03-08 mirrorLayer4 stl
2022-03-09 layer2 pdf
2022-03-09 layer2 ai file
2022-03-11 light sensor
2022-03-11 edited stuff
2022-03-11 argh dirbbler ausdhauidhiawd
2022-03-14 updated rollers stl
2022-03-21 added new cura
2022-03-22 i didnt know i didnt commit
2022-03-25 new drbbler wall
2022-03-25 layer 2 update + stl files
2022-03-26 purge
2022-03-30 stuff
2022-03-30 kicad
2022-03-30 gcode print
2022-04-01 sen logo
2022-04-01 layer 2 update
2022-04-03 layer2 brd changed
2022-04-03 bmp logo
2022-04-08 layer 4v5 dxf
2022-04-08 fixed buggy graphics folder gi
2022-04-08 layer 4 pcb
2022-04-09 layer4
2022-04-09 remove kicad
2022-04-14 Create LICENSE
2022-04-14 stl updates
2022-04-16 updated dribbler mount with stl
2022-04-18 dk what
2022-04-21 rearranged stl files, exported gcode part 1
2022-04-22 -g push
2022-04-22 r plate stl dribbler
2022-04-22 new g code print
2022-05-21 layer 4 ultrasonic
2023-06-11 submissions
